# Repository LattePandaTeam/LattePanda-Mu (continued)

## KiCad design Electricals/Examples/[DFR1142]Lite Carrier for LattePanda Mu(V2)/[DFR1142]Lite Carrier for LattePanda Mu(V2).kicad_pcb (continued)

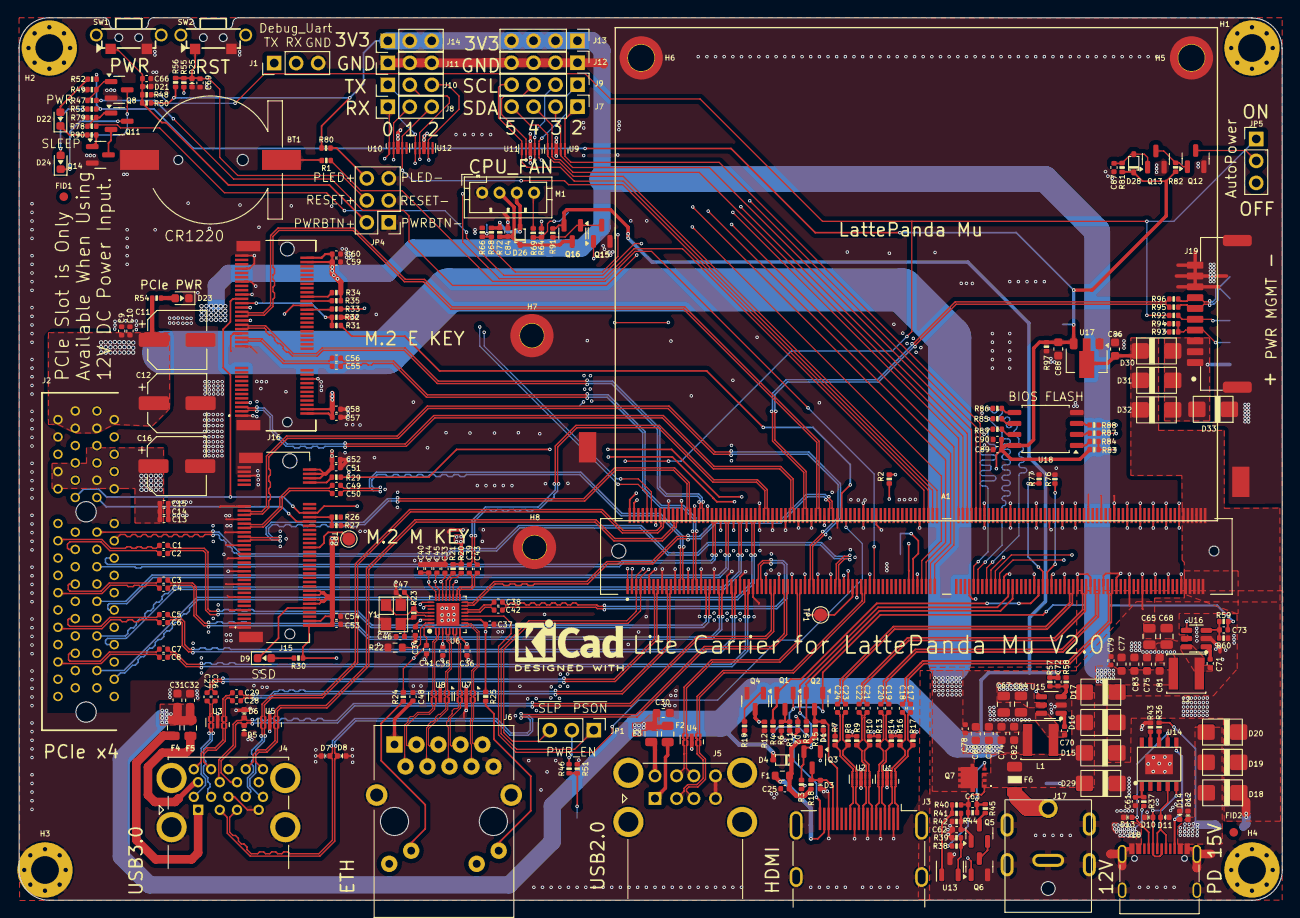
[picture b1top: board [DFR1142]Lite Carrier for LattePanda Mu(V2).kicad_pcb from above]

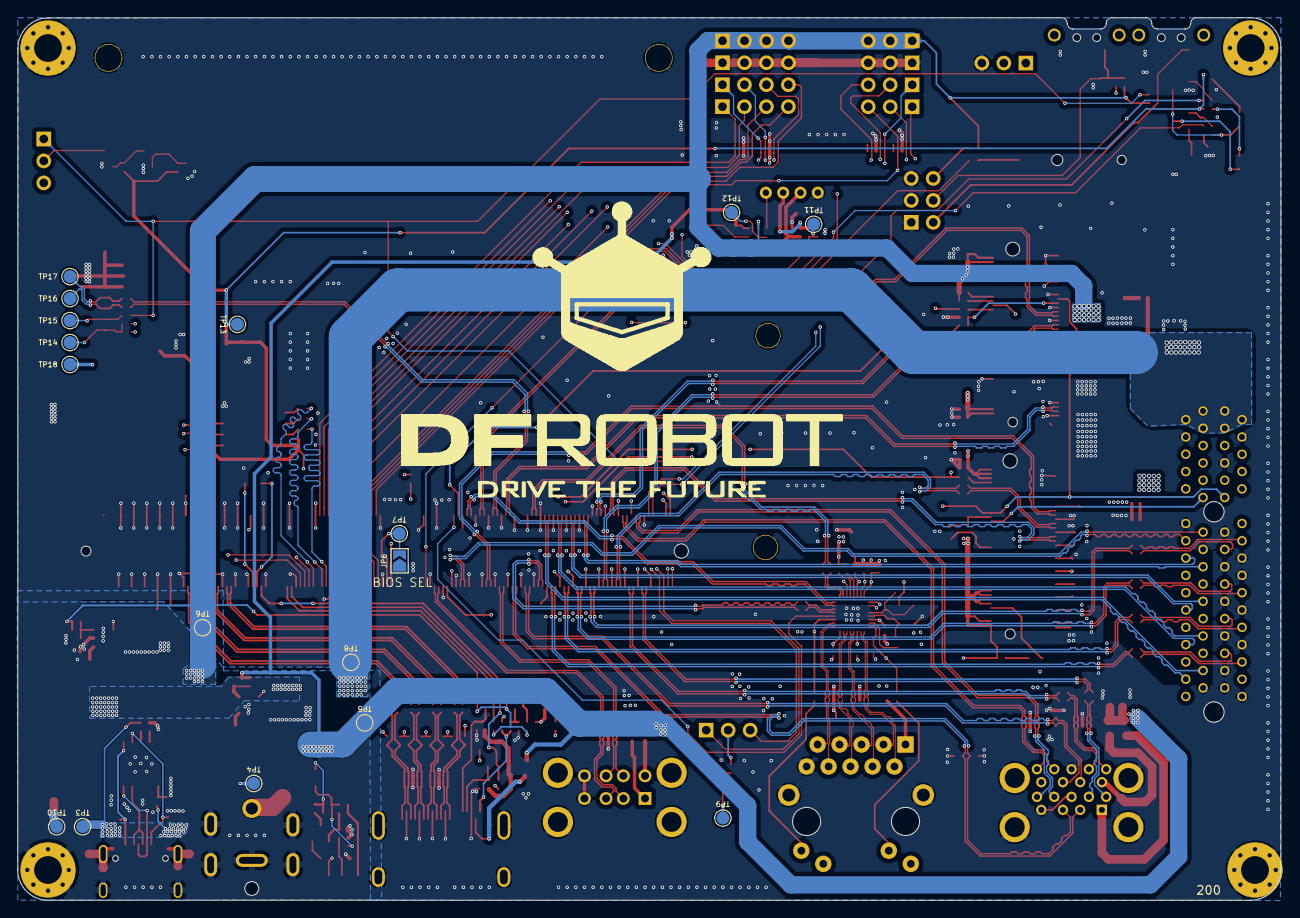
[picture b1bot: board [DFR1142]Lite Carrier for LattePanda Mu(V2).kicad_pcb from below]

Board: 4 copper layers, 146.0 x 102.0 mm, 304 parts (17 on the bottom side), 235 nets.

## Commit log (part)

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2024-04-04 Create README zh
2024-04-04 Upload libraries
2024-04-06 upload example project
2024-04-08 upload 3d models
2024-04-08 upload BIOS and tools
2024-04-09 upload drivers
2024-04-09 upload DFR1141 files
2024-04-09 DFR1141 readme
2024-04-09 BIOS readme
2024-04-09 drivers readme
2024-04-16 Update README.md
    update discord link
2024-04-27 update pinouts
2024-04-29 fix clkreq numbering error
2024-05-06 update espi contacts
2024-05-11 upload heatsink model
2024-05-13 create Chinese branch
2024-05-13 chinese link
2024-05-13 interpret
2024-05-13 translate
2024-05-16 upload 3dmodels
2024-05-16 upload pic
2024-05-24 Add files via upload
    nvme Carrier for LattePanda Mu
2024-05-24 Add README.md
2024-05-24 Add Images for Back and Front
2024-05-27 Some small changes
2024-05-30 small changes and optimizations
2024-06-02 Add BIOS Chip to Carrier
2024-06-05 upload debug bios
2024-06-17 Add BIOS Chip and small Changes to the Board
2024-06-17 GND opti
2024-06-21 Layout optimization + internal USB
2024-07-29 upload TGPIO BIOS
2024-08-05 Additional Pin Descriptions
2024-08-05 fix format
2024-08-19 upload dimension drawing
2024-09-25 Fix typo in pinout doc
    NOTE: GPD5 is supposed to be SLS_S4# & not SLS_S3# (which is GPD4 according to the datasheet) - left it as is, but may be worth a review.
2025-07-21 Add BIOS file for 16GB RAM model
2025-12-20 fix: back pinout should be FAN2_TAC rather than TAN2_TAC
2025-12-26 add new bios for lattepanda mu
2026-01-14 update edge connector pinout
2026-02-10 add kicad project of dfr1142 v2
2026-03-26 update bios readme
2026-06-03 Add DFR1144 GPU Carrier for LattePnada Mu
2026-06-09 add BIOS(supports I2C/GPIO in Windows)
2026-06-10 Optimize files
